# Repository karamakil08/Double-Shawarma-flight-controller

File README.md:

🚀 Double Shawarma: High-Performance Micro Drone
Double Shawarma is a custom-engineered, ultra-lightweight micro drone built on the ESP32-C3 architecture. Designed for agility and durability, this project pushes the limits of 1S-powered flight using 8.5mm coreless motors and a bespoke 3D-printed chassis optimized for maximum structural rigidity.

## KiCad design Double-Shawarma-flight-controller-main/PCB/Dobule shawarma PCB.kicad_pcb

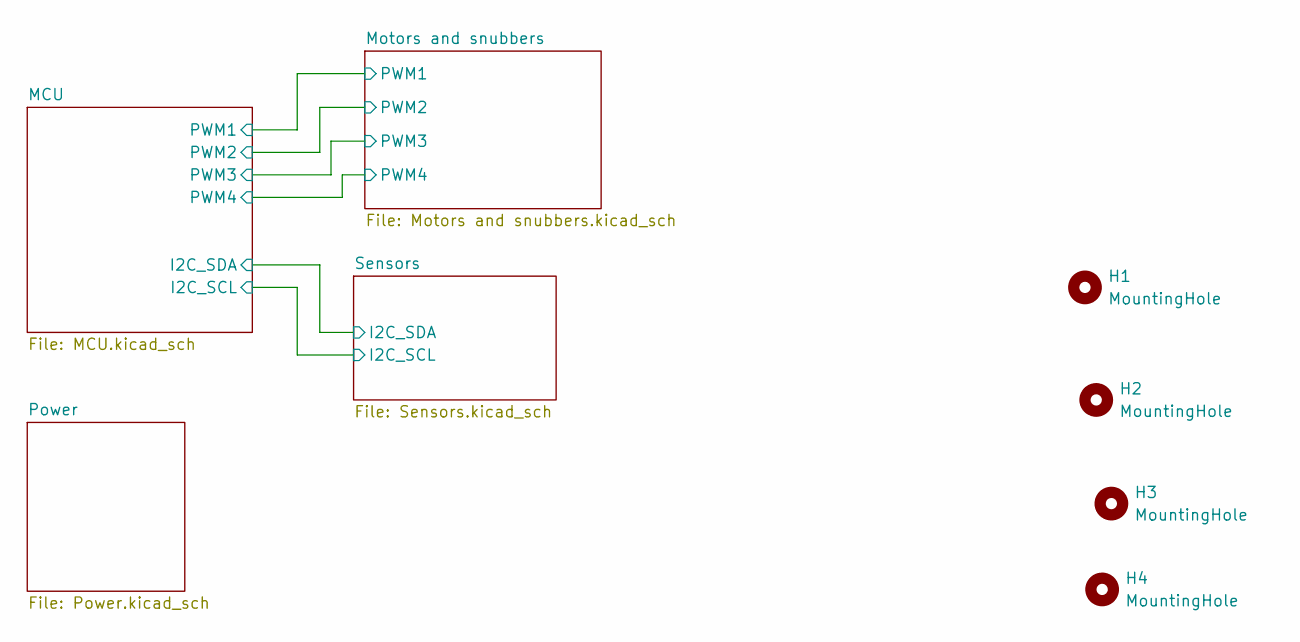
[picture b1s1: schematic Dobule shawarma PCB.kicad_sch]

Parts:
H1, H2, H3, H4: MountingHole; MountingHole_2.2mm_M2_Pad_Via

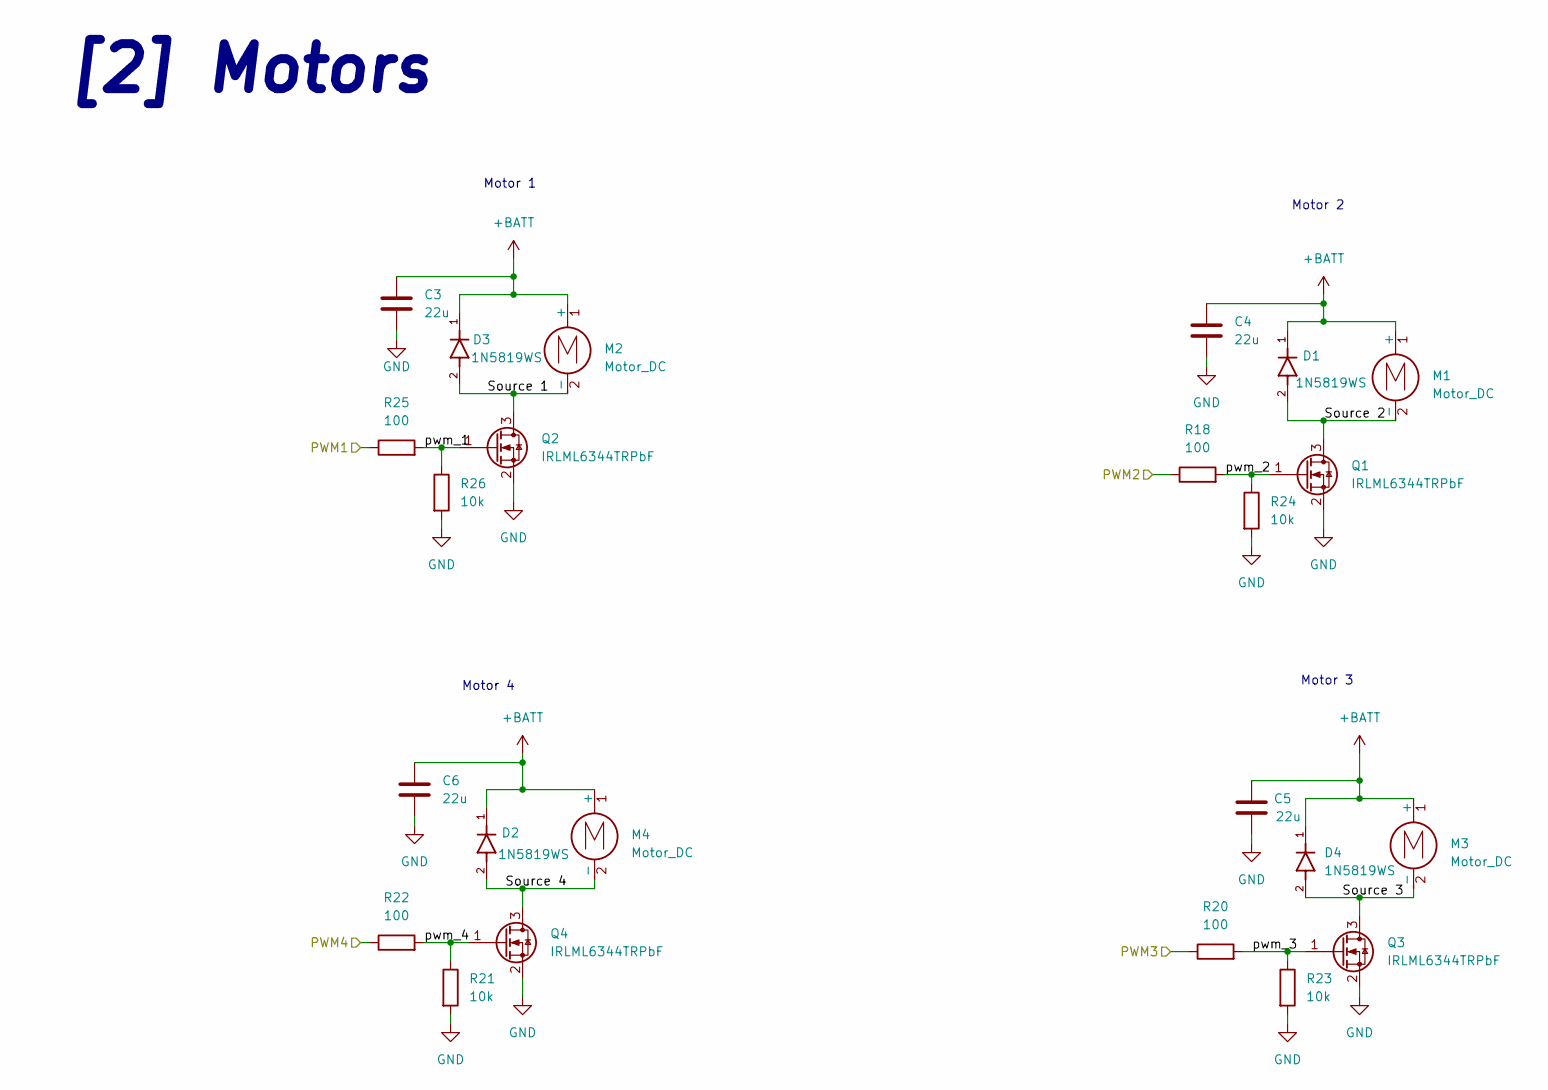
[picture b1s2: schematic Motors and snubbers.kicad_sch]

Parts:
C3, C4, C5, C6: 22u; C_0603_1608Metric_Pad1.08x0.95mm_HandSolder
D1, D2, D3, D4: 1N5819WS; CR_SOD323_MCC; PARTREV G
M1, M2, M3, M4: Motor_DC; TestPoint_Bridge_Pitch2.54mm_Drill0.7mm
Q1, Q2, Q3, Q4: IRLML6344TRPbF; SOT-23
R18, R20, R22, R25: 100; R_0603_1608Metric_Pad0.98x0.95mm_HandSolder
R21, R23, R24, R26: 10k; R_0603_1608Metric_Pad0.98x0.95mm_HandSolder

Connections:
+BATT: C3.2, C4.2, C5.2, C6.2, D1.1, D2.1, D3.1, D4.1, M1.1 (+), M2.1 (+), M3.1 (+), M4.1 (+); also elsewhere on the board
/MCU/PWM1: R25.1; also elsewhere on the board
/MCU/PWM2: R18.1; also elsewhere on the board
/MCU/PWM3: R20.1; also elsewhere on the board
/MCU/PWM4: R22.1; also elsewhere on the board
/Motors and snubbers/Source 1: D3.2, M2.2 (-), Q2.3 (D)
/Motors and snubbers/Source 2: D1.2, M1.2 (-), Q1.3 (D)
/Motors and snubbers/Source 3: D4.2, M3.2 (-), Q3.3 (D)
/Motors and snubbers/Source 4: D2.2, M4.2 (-), Q4.3 (D)
/Motors and snubbers/pwm_1: Q2.1 (G), R25.2, R26.1
/Motors and snubbers/pwm_2: Q1.1 (G), R18.2, R24.1
/Motors and snubbers/pwm_3: Q3.1 (G), R20.2, R23.1
/Motors and snubbers/pwm_4: Q4.1 (G), R21.1, R22.2
GND: C3.1, C4.1, C5.1, C6.1, Q1.2 (S), Q2.2 (S), Q3.2 (S), Q4.2 (S), R21.2, R23.2, R24.2, R26.2; also elsewhere on the board

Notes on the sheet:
Motor 3
Motor 2
Motor 1
[2] Motors
Motor 4

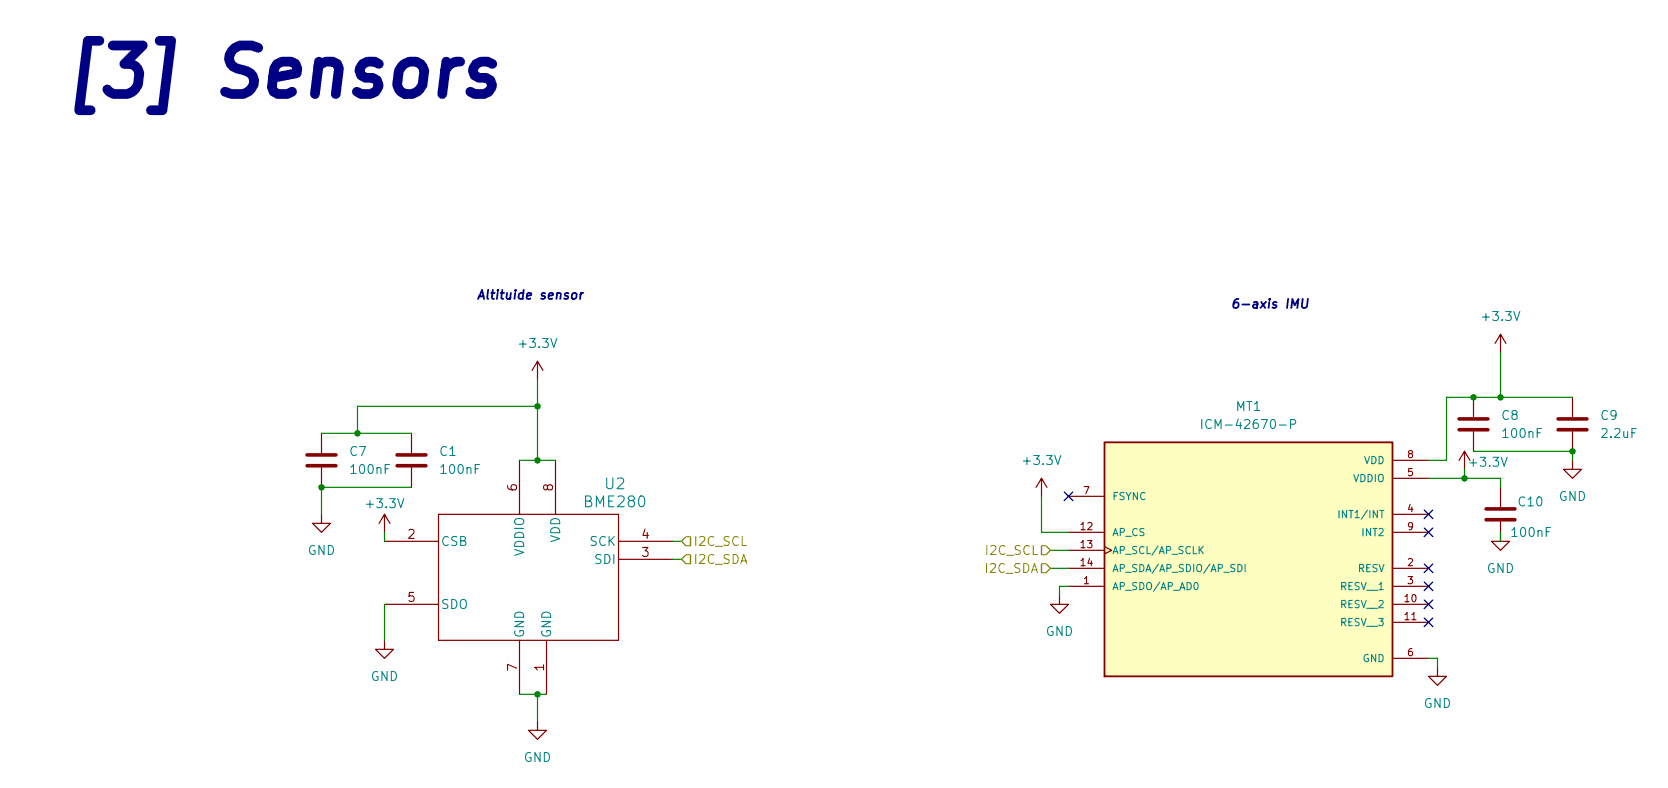
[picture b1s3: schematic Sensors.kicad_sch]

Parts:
C1, C7, C8, C10: 100nF; C_0603_1608Metric_Pad1.08x0.95mm_HandSolder
C9: 2.2uF; C_0603_1608Metric_Pad1.08x0.95mm_HandSolder
MT1: ICM-42670-P; XDCR_ICM-42670-P; PARTREV 1.1
U2: BME280; DFN8_0p65_2p5SQ_BOS

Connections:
+3.3V: C1.1, C7.1, C8.1, C9.1, C10.1, MT1.5 (VDDIO), MT1.8 (VDD), MT1.12 (AP_CS), U2.2 (CSB), U2.6 (VDDIO), U2.8 (VDD); also elsewhere on the board
/MCU/I2C_SCL: MT1.13 (AP_SCL/AP_SCLK), U2.4 (SCK); also elsewhere on the board
/MCU/I2C_SDA: MT1.14 (AP_SDA/AP_SDIO/AP_SDI), U2.3 (SDI); also elsewhere on the board
GND: C1.2, C7.2, C8.2, C9.2, C10.2, MT1.1 (AP_SDO/AP_AD0), MT1.6 (GND), U2.1 (GND), U2.5 (SDO), U2.7 (GND); also elsewhere on the board

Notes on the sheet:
6-axis IMU
Altituide sensor
[3] Sensors

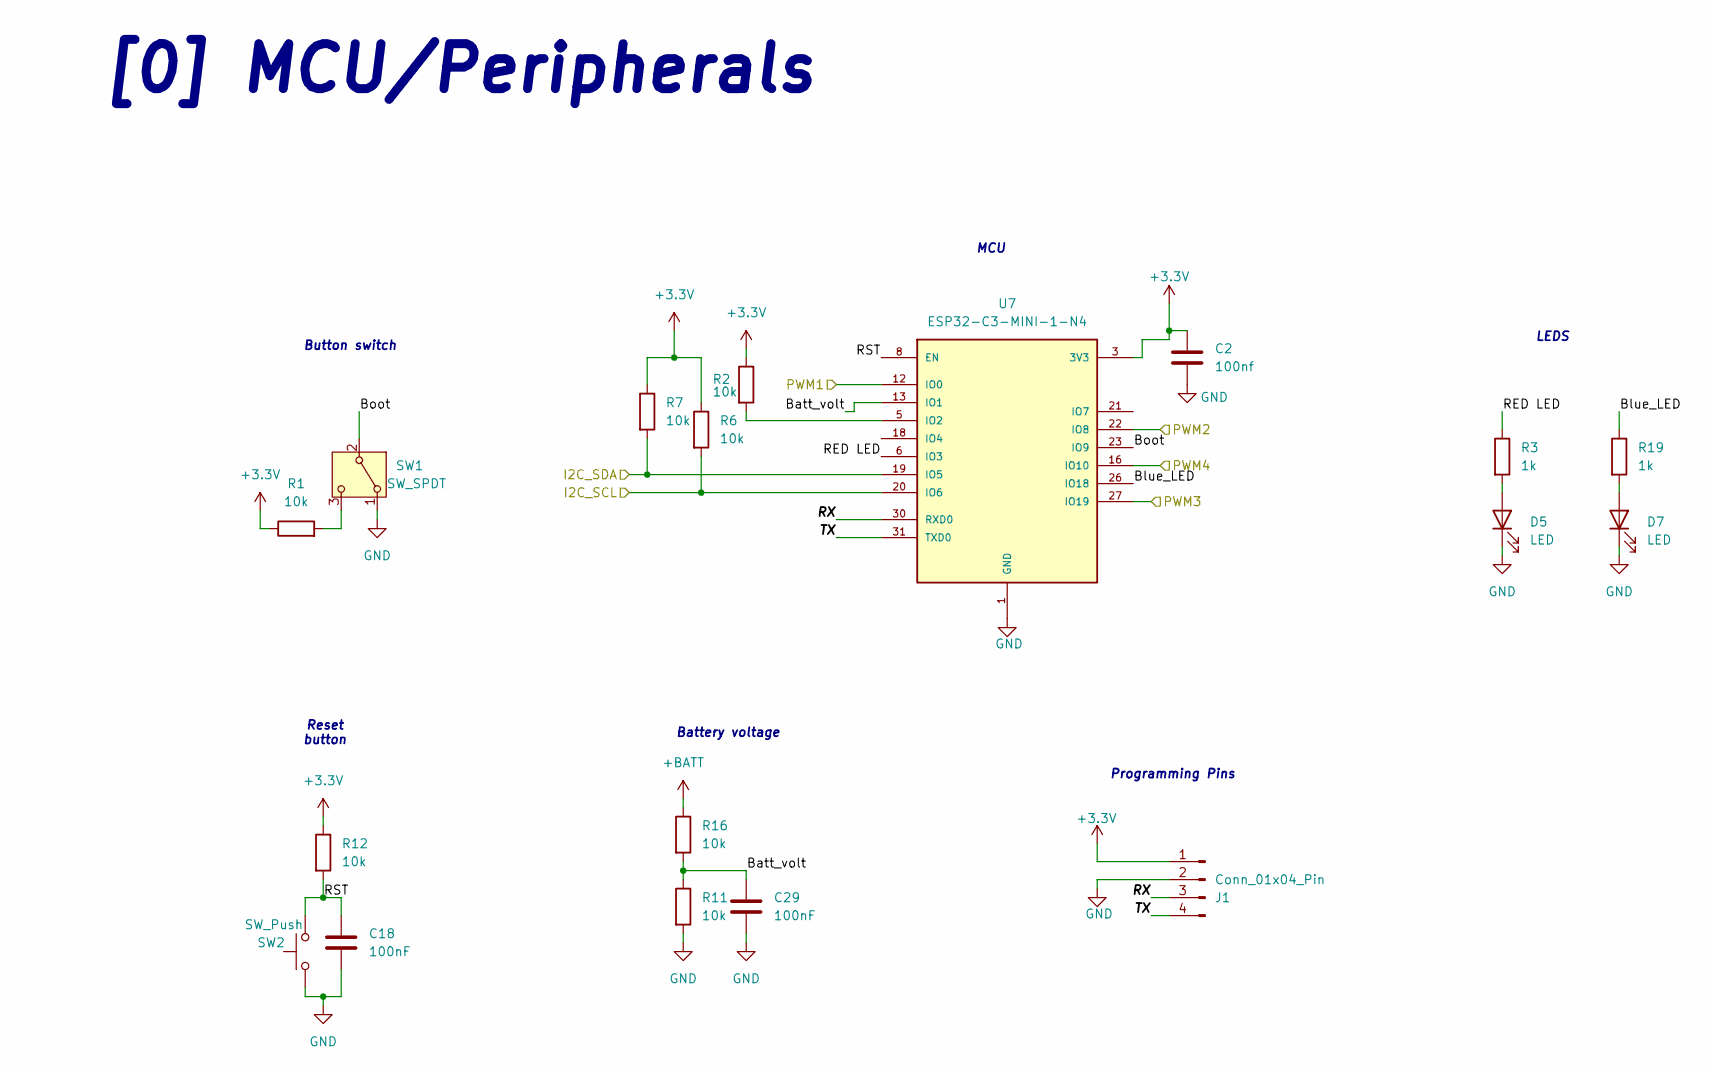
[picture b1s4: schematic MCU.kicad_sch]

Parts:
C2: 100nf; C_0603_1608Metric_Pad1.08x0.95mm_HandSolder
C18, C29: 100nF; C_0603_1608Metric_Pad1.08x0.95mm_HandSolder
D5, D7: LED; LED_0603_1608Metric_Pad1.05x0.95mm_HandSolder
J1: Conn_01x04_Pin; PinHeader_1x04_P1.00mm_Vertical
R1, R2: 10k; R_0603_1608Metric
R3, R19: 1k; R_0603_1608Metric_Pad0.98x0.95mm_HandSolder
R6, R7, R11, R12, R16: 10k; R_0603_1608Metric_Pad0.98x0.95mm_HandSolder
SW1: SW_SPDT; SW_SPDT_PCM12
SW2: SW_Push; SW_SPST_PTS810
U7: ESP32-C3-MINI-1-N4; XCVR_ESP32-C3-MINI-1-N4; PARTREV v1.0

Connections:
+3.3V: C2.1, J1.1, R1.1, R2.1, R6.1, R7.1, R12.1, U7.3 (3V3); also elsewhere on the board
+BATT: R16.1; also elsewhere on the board
/MCU/Batt_volt: C29.1, R11.1, R16.2, U7.13 (IO1)
/MCU/Blue_LED: R19.1, U7.26 (IO18)
/MCU/Boot: SW1.2 (B), U7.23 (IO9)
/MCU/I2C_SCL: R6.2, U7.20 (IO6); also elsewhere on the board
/MCU/I2C_SDA: R7.2, U7.19 (IO5); also elsewhere on the board
/MCU/PWM1: U7.12 (IO0); also elsewhere on the board
/MCU/PWM2: U7.22 (IO8); also elsewhere on the board
/MCU/PWM3: U7.27 (IO19); also elsewhere on the board
/MCU/PWM4: U7.16 (IO10); also elsewhere on the board
/MCU/RED LED: R3.1, U7.6 (IO3)
/MCU/RST: C18.1, R12.2, SW2.2, U7.8 (EN)
/MCU/RX: J1.3, U7.30 (RXD0)
/MCU/TX: J1.4, U7.31 (TXD0)
GND: C2.2, C18.2, C29.2, D5.1 (K), D7.1 (K), J1.2, R11.2, SW1.1 (A), SW2.1, U7.1 (GND), U7.2 (GND__1), U7.11 (GND__2), U7.14 (GND__3), U7.36 (GND__4), U7.37 (GND__5), U7.38 (GND__6), U7.39 (GND__7), U7.40 (GND__8), U7.41 (GND__9), U7.42 (GND__10), U7.43 (GND__11), U7.44 (GND__12), U7.45 (GND__13), U7.46 (GND__14), U7.47 (GND__15), U7.48 (GND__16), U7.49_1 (GND__17), U7.49_2 (GND__18), U7.49_3 (GND__19), U7.49_4 (GND__20), U7.49_5 (GND__21), U7.49_6 (GND__22), U7.49_7 (GND__23), U7.49_8 (GND__24), U7.49_9 (GND__25), U7.50 (GND__26), U7.51 (GND__27), U7.52 (GND__28), U7.53 (GND__29); also elsewhere on the board
unnamed: D5.2 (A), R3.2
unnamed: D7.2 (A), R19.2
unnamed: R1.2, SW1.3 (C)
unnamed: R2.2, U7.5 (IO2)

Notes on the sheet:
MCU
LEDS
Reset button
[0] MCU/Peripherals
Button switch
Programming Pins
Battery voltage

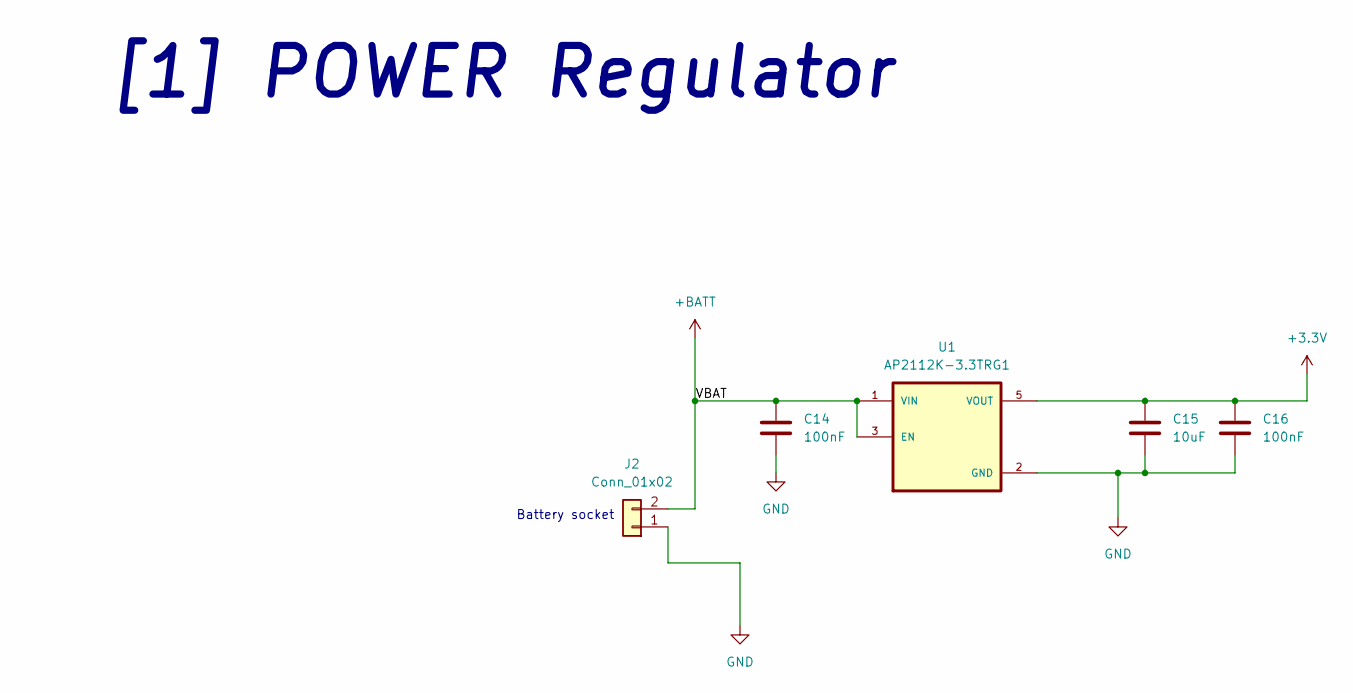
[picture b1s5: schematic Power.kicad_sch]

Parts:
C14, C16: 100nF; C_0603_1608Metric_Pad1.08x0.95mm_HandSolder
C15: 10uF; CP_EIA-3216-18_Kemet-A_HandSolder
J2: Conn_01x02; JST_PH_S2B-PH-K_1x02_P2.00mm_Horizontal
U1: AP2112K-3.3TRG1; SOT95P285X140-5N; PARTREV 2-2

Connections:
+3.3V: C15.1, C16.1, U1.5 (VOUT); also elsewhere on the board
+BATT: C14.1, J2.2, U1.1 (VIN), U1.3 (EN); also elsewhere on the board
GND: C14.2, C15.2, C16.2, J2.1, U1.2 (GND); also elsewhere on the board

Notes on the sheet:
[1] POWER Regulator
Battery socket

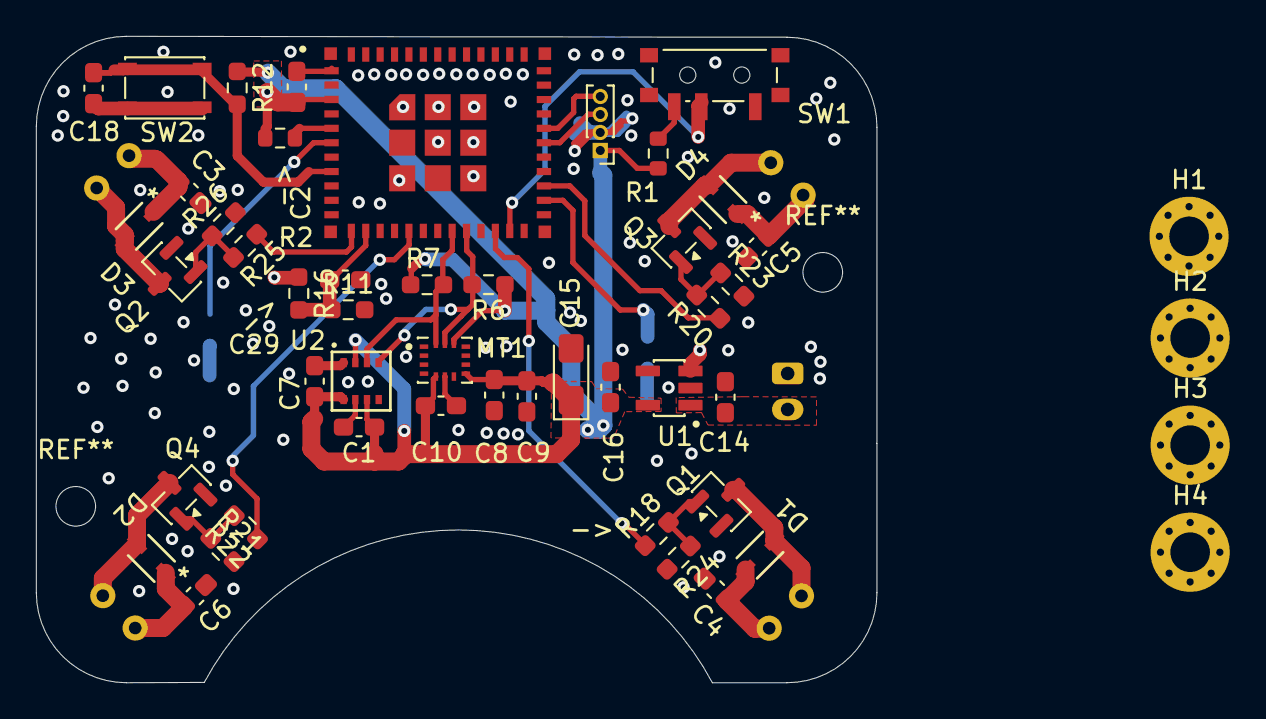
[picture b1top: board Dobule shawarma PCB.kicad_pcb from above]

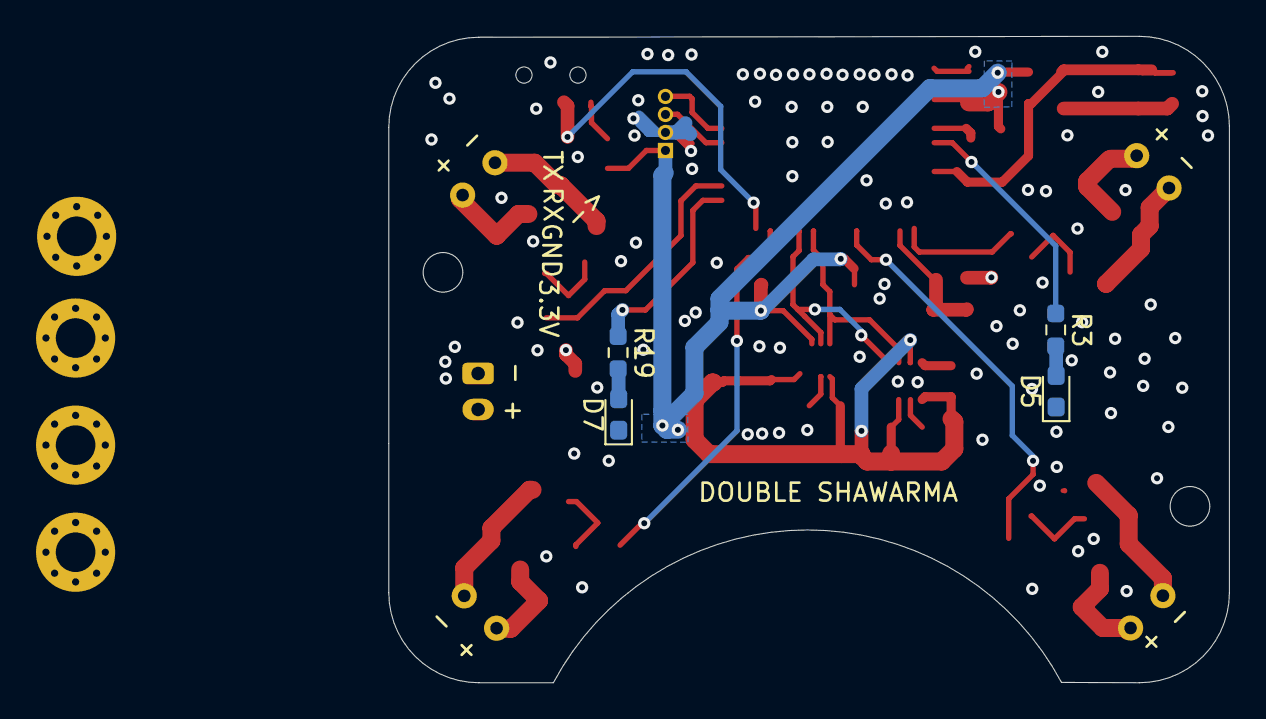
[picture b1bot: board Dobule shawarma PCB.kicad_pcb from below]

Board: 4 copper layers, 46.7 x 35.9 mm, 58 parts (4 on the bottom side), 28 nets.

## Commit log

2026-04-21 Final: Dobule Shawarma PCB v1 ve 0.143mm sasi hazir
2026-04-21 Final: Organized into Hardware, Production and Chassis folders
2026-04-22 Add project description to README
    Add project overview for Double Shawarma micro drone.
2026-04-30 Bak bu harbi son olsun yeter amk
2026-04-30 Bu son olsun dostum
